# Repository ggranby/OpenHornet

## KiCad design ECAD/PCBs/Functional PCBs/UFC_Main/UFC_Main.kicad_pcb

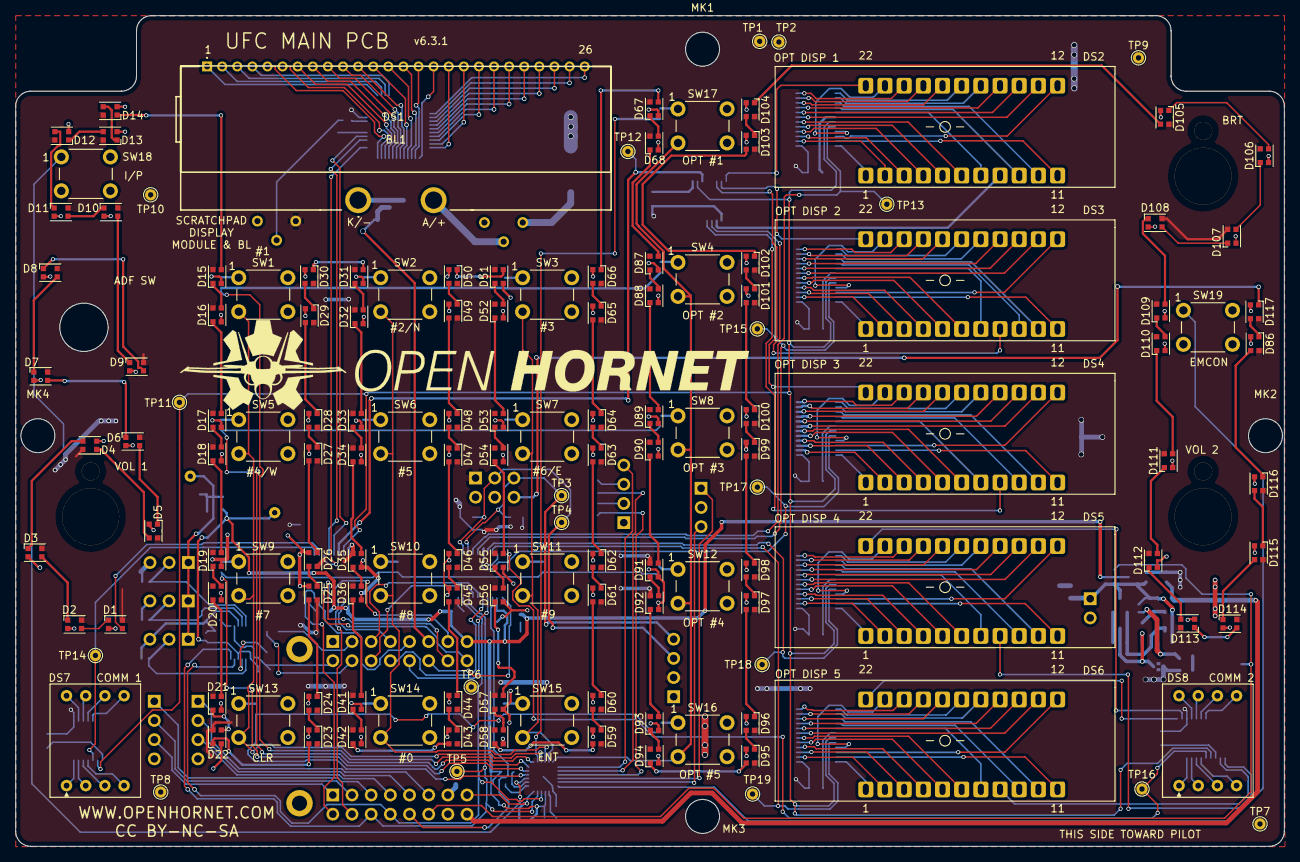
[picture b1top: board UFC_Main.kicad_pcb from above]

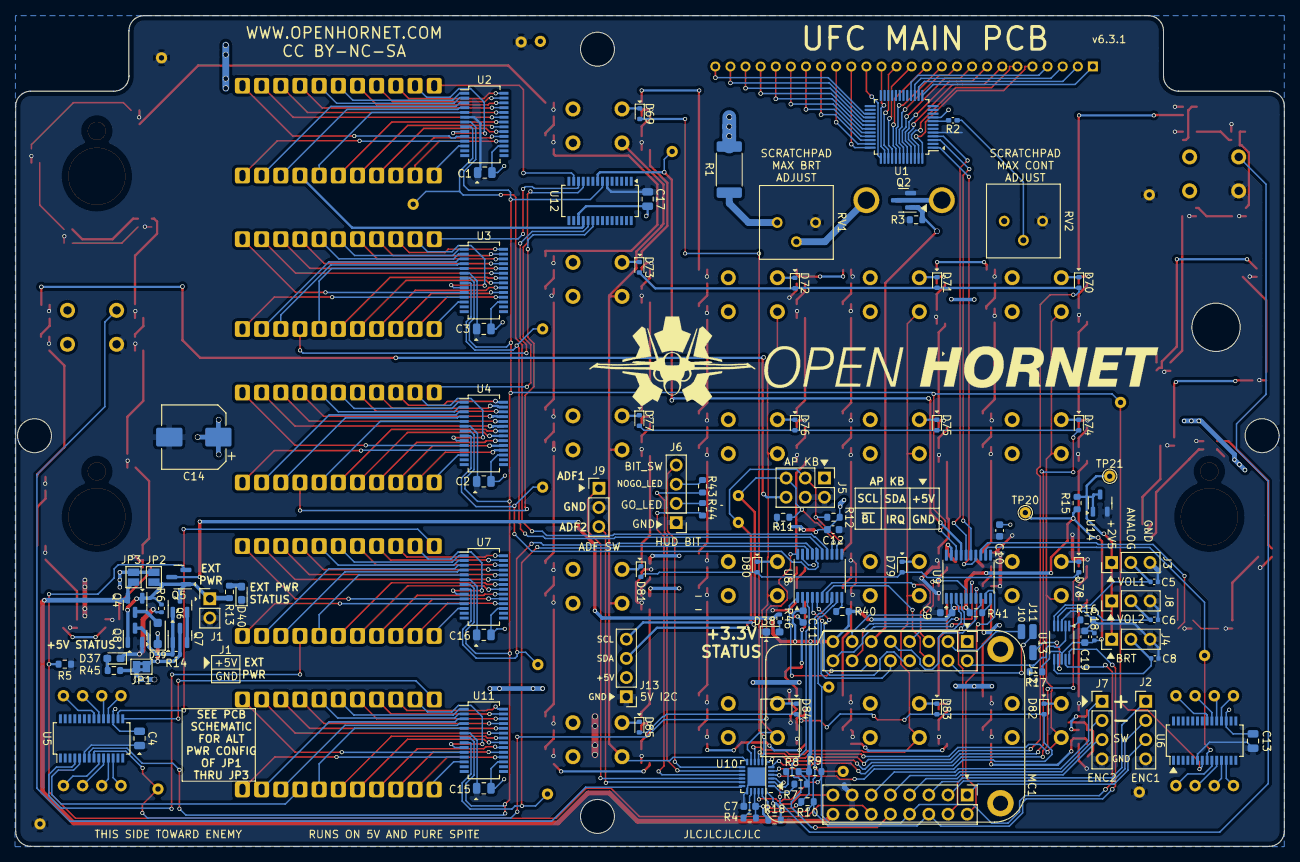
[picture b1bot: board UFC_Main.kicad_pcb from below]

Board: 2 copper layers, 168.0 x 110.0 mm, 257 parts (105 on the bottom side), 353 nets.

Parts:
BL1: SCR BL; SCRATCHPADBACKLIGHT
C1, C2, C3, C4, C13, C15, C16, C17: 10uF; C_0805_2012Metric
C5, C6, C8: 100nF; C_0402_1005Metric
C7, C9, C10, C11, C12, C19: .1uF; C_0603_1608Metric
C14: 1000uF; CP_Elec_8x10
C18: 10uF; C_0402_1005Metric
D1, D2, D3, D4, D5, D6, D7, D8, D9, D10, D11, D12, D13, D14, D15, D16, D17, D18, D19, D20, D21, D22, D23, D24, D25, D26, D27, D28, D29, D30, D31, D32, D33, D34, D35, D36, D41, D42, D43, D44, D45, D46, D47, D48, D49, D50, D51, D52, D53, D54, D55, D56, D57, D58, D59, D60, D61, D62, D63, D64, D65, D66, D67, D68, D86, D87, D88, D89, D90, D91, D92, D93, D94, D95, D96, D97, D98, D99, D100, D101, D102, D103, D104, D105, D106, D107, D108, D109, D110, D111, D112, D113, D114, D115, D116, D117: WS2812B-2020; LED_WS2812B-2020_PLCC4_2.0x2.0mm
D37: +5V_PWR; LED_0603_1608Metric_Pad1.05x0.95mm_HandSolder
D38: +3.3V_PWR; LED_0603_1608Metric_Pad1.05x0.95mm_HandSolder
D39: K24; D_SOD-123F
D40: EXT PWR; LED_0603_1608Metric_Pad1.05x0.95mm_HandSolder
D69, D70, D71, D72, D73, D74, D75, D76, D77, D78, D79, D80, D81, D82, D83, D84, D85: 1N4148WT; D_SOD-523
DS1: SCR DISP; SCRATCHPADLCD
DS2, DS3, DS4, DS5, DS6: UFCOptionDigit; UFCOptionDigitV3RectanglePads
DS7, DS8: UFCSingleDigit
J1: EXT_PWR; PinHeader_1x02_P2.54mm_Vertical
J2: ENC1; PinHeader_1x04_P2.54mm_Vertical
J3: VOL1; PinHeader_1x03_P2.54mm_Vertical
J4: BRT; PinHeader_1x03_P2.54mm_Vertical
J5: AP KB; PinHeader_2x03_P2.54mm_Vertical
J6: HUD BIT; PinHeader_1x04_P2.54mm_Vertical
J7: ENC2; PinHeader_1x04_P2.54mm_Vertical
J8: VOL2; PinHeader_1x03_P2.54mm_Vertical
J9: ADF SW; PinHeader_1x03_P2.54mm_Vertical
J10: GPIO3; SolderWirePad_1x01_SMD_1x2mm
J11: GPIO2; SolderWirePad_1x01_SMD_1x2mm
J12: AIN3; SolderWirePad_1x01_SMD_1x2mm
J13: 5V I2C; PinHeader_1x04_P2.54mm_Vertical
JP1: 5VP; SolderJumper-2_P1.3mm_Bridged2Bar_Pad1.0x1.5mm
JP2: VCC; SolderJumper-2_P1.3mm_Open_Pad1.0x1.5mm
JP3: VBUS; SolderJumper-2_P1.3mm_Open_Pad1.0x1.5mm
LOGO: LOGO; LOGO_OH_Text_Large
MC1: S2_MINI
MK1, MK2, MK3, MK4: MH; MountingHole_4.5mm
MK5: SW_ADF; MountingHole_6.4mm_M6
POT1: VOL1; BR10K_Pot_11mm_x_11mm
POT2: VOL2; BR10K_Pot_11mm_x_11mm
POT3: BRT; BR10K_Pot_11mm_x_11mm
Q2: 2N7002; SOT-23
Q4, Q6, Q7: SKML5203; SOT-23
Q5, Q8: SI2302; SOT-23
R1: 10; R_2512_6332Metric_Pad1.40x3.35mm_HandSolder
R2: 10; C_0402_1005Metric_Pad0.74x0.62mm_HandSolder
R3, R5, R7, R8: 10K; R_0603_1608Metric
R4, R9, R10, R11, R12, R18, R40, R41: 4.7k; R_0603_1608Metric
R6, R14: 100K; R_0402_1005Metric
R13, R15, R43, R44, R45: 120; R_0603_1608Metric
R16, R17: 4.7K; R_0603_1608Metric
R46: 33; R_0402_1005Metric
RV1: 1K; Potentiometer_Bourns_3386P_Vertical
RV2: 10K; Potentiometer_Bourns_3386P_Vertical
SW1, SW2, SW3, SW4, SW5, SW6, SW7, SW8, SW9, SW10, SW11, SW12, SW13, SW14, SW15, SW16, SW17, SW18, SW19: B3F-1026; Omron_B3F-1026
TP1: 5V; TestPoint_THTPad_D1.5mm_Drill0.7mm
TP2, TP7, TP8, TP9, TP10: GND; TestPoint_THTPad_D1.5mm_Drill0.7mm
TP3: SCL; TestPoint_THTPad_D1.5mm_Drill0.7mm
TP4: SDA; TestPoint_THTPad_D1.5mm_Drill0.7mm
TP5: SCL@3.3V; TestPoint_THTPad_D1.5mm_Drill0.7mm
TP6: SDA@3.3V; TestPoint_THTPad_D1.5mm_Drill0.7mm
TP11: DIO; TestPoint_THTPad_D1.5mm_Drill0.7mm
TP12: CUE_CLK; TestPoint_THTPad_D1.5mm_Drill0.7mm
TP13: OP1_CLK; TestPoint_THTPad_D1.5mm_Drill0.7mm
TP14: C1_CLK; TestPoint_THTPad_D1.5mm_Drill0.7mm
TP15: OP2_CLK; TestPoint_THTPad_D1.5mm_Drill0.7mm
TP16: C2_CLK; TestPoint_THTPad_D1.5mm_Drill0.7mm
TP17: OP3_CLK; TestPoint_THTPad_D1.5mm_Drill0.7mm
TP18: OP4_CLK; TestPoint_THTPad_D1.5mm_Drill0.7mm
TP19: OP5_CLK; TestPoint_THTPad_D1.5mm_Drill0.7mm
TP20: 3V3; TestPoint_THTPad_D1.5mm_Drill0.7mm
TP21: 2V5; TestPoint_THTPad_D1.5mm_Drill0.7mm
U1: HT1621B; LQFP-48_7x7mm_P0.5mm
U2, U3, U4, U5, U6, U7, U11, U12: GN1640T; SSOP-28_3.9x9.9mm_P0.635mm
U8, U9: TXS0108EPWR; TSSOP-20_4.4x6.5mm_P0.65mm
U10: TCA8418RTWR; WQFN-24-1EP_4x4mm_P0.5mm_EP2.45x2.45mm
U13: ADS1115IDGSR; VSSOP-10_3x3mm_P0.5mm
U14: ADR5040ARTZ; SOT-23-3

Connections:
+2V5: J3.1, J4.1, J8.1, R15.2, TP21.1 (1_1), U14.1 (V+), U14.3 (T)
+3V3: C7.2, C9.2, C11.2, C18.2, C19.2, MC1.8 (+3.3V), Q5.3 (D), R4.1, R7.2, R8.2, R9.1, R10.2, R15.1, R17.1, R18.1, R40.2, R41.2, R46.1, TP20.1 (1_1), U8.2 (VCCA), U9.2 (VCCA), U10.21 (VCC), U13.8 (VDD)
+5V: C1.2, C2.2, C3.2, C4.2, C10.2, C12.2, C13.2, C14.1, C15.2, C16.2, C17.2, D1.4 (VSS), D2.4 (VSS), D3.4 (VSS), D4.4 (VSS), D5.4 (VSS), D6.4 (VSS), D7.4 (VSS), D8.4 (VSS), D9.4 (VSS), D10.4 (VSS), D11.4 (VSS), D12.4 (VSS), D13.4 (VSS), D14.4 (VSS), D15.4 (VSS), D16.4 (VSS), D17.4 (VSS), D18.4 (VSS), D19.4 (VSS), D20.4 (VSS), D21.4 (VSS), D22.4 (VSS), D23.4 (VSS), D24.4 (VSS), D25.4 (VSS), D26.4 (VSS), D27.4 (VSS), D28.4 (VSS), D29.4 (VSS), D30.4 (VSS), D31.4 (VSS), D32.4 (VSS), D33.4 (VSS), D34.4 (VSS), D35.4 (VSS), D36.4 (VSS), D41.4 (VSS), D42.4 (VSS), D43.4 (VSS), D44.4 (VSS), D45.4 (VSS), D46.4 (VSS), D47.4 (VSS), D48.4 (VSS), D49.4 (VSS), D50.4 (VSS), D51.4 (VSS), D52.4 (VSS), D53.4 (VSS), D54.4 (VSS), D55.4 (VSS), D56.4 (VSS), D57.4 (VSS), D58.4 (VSS), D59.4 (VSS), D60.4 (VSS), D61.4 (VSS), D62.4 (VSS), D63.4 (VSS), D64.4 (VSS), D65.4 (VSS), D66.4 (VSS), D67.4 (VSS), D68.4 (VSS), D86.4 (VSS), D87.4 (VSS), D88.4 (VSS), D89.4 (VSS), D90.4 (VSS), D91.4 (VSS), D92.4 (VSS), D93.4 (VSS), D94.4 (VSS), D95.4 (VSS), D96.4 (VSS), D97.4 (VSS), D98.4 (VSS), D99.4 (VSS), D100.4 (VSS), D101.4 (VSS), D102.4 (VSS), D103.4 (VSS), D104.4 (VSS), D105.4 (VSS), D106.4 (VSS), D107.4 (VSS), D108.4 (VSS), D109.4 (VSS), D110.4 (VSS), D111.4 (VSS), D112.4 (VSS), D113.4 (VSS), D114.4 (VSS), D115.4 (VSS), D116.4 (VSS), D117.4 (VSS), J5.1, J13.2, JP1.2 (B), JP2.2 (B), JP3.2 (B), R1.2, R11.1, R12.2, R45.1, RV2.1, TP1.1 (1_1), U1.9 (VDD), U2.17 (VDD), U3.17 (VDD), U4.17 (VDD), U5.17 (VDD), U6.17 (VDD), U7.17 (VDD), U8.19 (VCCB), U9.19 (VCCB), U11.17 (VDD), U12.17 (VDD)
/1A: DS2.20 (A), U2.28 (GRID11)
/1B: DS2.19 (B), U2.27 (GRID10)
/1C: DS2.18 (C), U2.26 (GRID9)
/1D: DS2.2 (D), U2.18 (GRID1)
/1DP: DS2.8 (C5/D5), U12.18 (GRID1)
/1E: DS2.3 (E), U2.19 (GRID2)
/1F: DS2.4 (F), U2.20 (GRID3)
/1G: DS2.5 (G), U2.21 (GRID4)
/1H: DS2.6 (H), U2.22 (GRID5)
/1I: DS2.13 (I), U2.23 (GRID6)
/1J: DS2.14 (J), U2.24 (GRID7)
/1K: DS2.15 (K), U2.25 (GRID8)
/1L: DS2.16 (L), U2.2 (GRID13)
/1M: DS2.17 (M), U2.1 (GRID12)
/1N: DS2.9 (N), U2.4 (GRID15)
/1O: DS2.10 (O), U2.3 (GRID14)
/1P: DS2.7, U2.5 (GRID16)
/2A: DS3.20 (A), U3.28 (GRID11)
/2B: DS3.19 (B), U3.27 (GRID10)
/2C: DS3.18 (C), U3.26 (GRID9)
/2D: DS3.2 (D), U3.18 (GRID1)
/2DP: DS3.8 (C5/D5), U12.19 (GRID2)
/2E: DS3.3 (E), U3.19 (GRID2)
/2F: DS3.4 (F), U3.20 (GRID3)
/2G: DS3.5 (G), U3.21 (GRID4)
/2H: DS3.6 (H), U3.22 (GRID5)
/2I: DS3.13 (I), U3.23 (GRID6)
/2J: DS3.14 (J), U3.24 (GRID7)
/2K: DS3.15 (K), U3.25 (GRID8)
/2L: DS3.16 (L), U3.2 (GRID13)
/2M: DS3.17 (M), U3.1 (GRID12)
/2N: DS3.9 (N), U3.4 (GRID15)
/2O: DS3.10 (O), U3.3 (GRID14)
/2P: DS3.7, U3.5 (GRID16)
/3A: DS4.20 (A), U4.28 (GRID11)
/3B: DS4.19 (B), U4.27 (GRID10)
/3C: DS4.18 (C), U4.26 (GRID9)
/3D: DS4.2 (D), U4.18 (GRID1)
/3DP: DS4.8 (C5/D5), U12.20 (GRID3)
/3E: DS4.3 (E), U4.19 (GRID2)
/3F: DS4.4 (F), U4.20 (GRID3)
/3G: DS4.5 (G), U4.21 (GRID4)
/3H: DS4.6 (H), U4.22 (GRID5)
/3I: DS4.13 (I), U4.23 (GRID6)
/3J: DS4.14 (J), U4.24 (GRID7)
/3K: DS4.15 (K), U4.25 (GRID8)
/3L: DS4.16 (L), U4.2 (GRID13)
/3M: DS4.17 (M), U4.1 (GRID12)
/3N: DS4.9 (N), U4.4 (GRID15)
/3O: DS4.10 (O), U4.3 (GRID14)
/3P: DS4.7, U4.5 (GRID16)
/4A: DS5.20 (A), U7.28 (GRID11)
/4B: DS5.19 (B), U7.27 (GRID10)
/4C: DS5.18 (C), U7.26 (GRID9)
/4D: DS5.2 (D), U7.18 (GRID1)
/4DP: DS5.8 (C5/D5), U5.4 (GRID15)
/4E: DS5.3 (E), U7.19 (GRID2)
/4F: DS5.4 (F), U7.20 (GRID3)
/4G: DS5.5 (G), U7.21 (GRID4)
/4H: DS5.6 (H), U7.22 (GRID5)
/4I: DS5.13 (I), U7.23 (GRID6)
/4J: DS5.14 (J), U7.24 (GRID7)
/4K: DS5.15 (K), U7.25 (GRID8)
/4L: DS5.16 (L), U7.2 (GRID13)
/4M: DS5.17 (M), U7.1 (GRID12)
/4N: DS5.9 (N), U7.4 (GRID15)
/4O: DS5.10 (O), U7.3 (GRID14)
/4P: DS5.7, U7.5 (GRID16)
/5A: DS6.20 (A), U11.28 (GRID11)
/5B: DS6.19 (B), U11.27 (GRID10)
/5C: DS6.18 (C), U11.26 (GRID9)
/5D: DS6.2 (D), U11.18 (GRID1)
/5DP: DS6.8 (C5/D5), U5.5 (GRID16)
/5E: DS6.3 (E), U11.19 (GRID2)
/5F: DS6.4 (F), U11.20 (GRID3)
/5G: DS6.5 (G), U11.21 (GRID4)
/5H: DS6.6 (H), U11.22 (GRID5)
/5I: DS6.13 (I), U11.23 (GRID6)
/5J: DS6.14 (J), U11.24 (GRID7)
/5K: DS6.15 (K), U11.25 (GRID8)
/5L: DS6.16 (L), U11.2 (GRID13)
/5M: DS6.17 (M), U11.1 (GRID12)
/5N: DS6.9 (N), U11.4 (GRID15)
/5O: DS6.10 (O), U11.3 (GRID14)
/5P: DS6.7, U11.5 (GRID16)
/ADF1: J9.1, U10.16 (COL7)
/ADF2: J9.3, U10.17 (COL8)
/AIN0: C6.2, J8.2, U13.4 (AIN0)
/AIN1: C5.2, J3.2, U13.5 (AIN1)
/AIN2: C8.2, J4.2, U13.6 (AIN2)
/BIT_SW: J6.4, U10.13 (COL4)
/BL_DATA2: D8.1 (DOUT), D9.3 (DIN)
/BL_DATA3: D16.1 (DOUT), D17.3 (DIN)
/BL_DATA4: D24.1 (DOUT), D25.3 (DIN)
/BL_DATA5: D32.1 (DOUT), D33.3 (DIN)
/BL_DATA6: D44.1 (DOUT), D45.3 (DIN)
/BL_DATA7: D52.1 (DOUT), D53.3 (DIN)
/BL_DATA8: D60.1 (DOUT), D61.3 (DIN)
/BL_DATA9: D68.1 (DOUT), D87.3 (DIN)
/BL_DATA10: D93.1 (DOUT), D94.3 (DIN)
/BL_DATA11: D101.1 (DOUT), D102.3 (DIN)
/BL_DATA12: D109.1 (DOUT), D110.3 (DIN)
/C1_GRID1: DS7.8, U6.18 (GRID1)
/C1_GRID2: DS7.7, U6.19 (GRID2)
/C1_GRID3: DS7.6, U6.20 (GRID3)
/C1_GRID4: DS7.5, U6.21 (GRID4)
/C1_SEG1: DS7.4, U6.9 (SEG1)
/C1_SEG2: DS7.3, U6.10 (SEG2)
/C1_SEG3: DS7.2, U6.11 (SEG3)
/C1_SEG4: DS7.1, U6.12 (SEG4)
/COL0: SW1.3, SW5.3, SW9.3, SW13.3, U10.9 (COL0)
/COL1: SW2.3, SW6.3, SW10.3, SW14.3, U10.10 (COL1)
/COL2: SW3.3, SW7.3, SW11.3, SW15.3, U10.11 (COL2)
/COL3: SW4.3, SW8.3, SW12.3, SW16.3, SW17.3, U10.12 (COL3)
/COM0: DS1.1 (COM1), U1.13 (COM0)
/COM1: DS1.2 (COM2), U1.14 (COM1)
/COM2: DS1.3 (COM3), U1.15 (COM2)
/COM3: DS1.4 (COM4), U1.16 (COM3)
/C_GRID1: DS8.8, U5.18 (GRID1)
/C_GRID2: DS8.7, U5.19 (GRID2)
/C_GRID3: DS8.6, U5.20 (GRID3)
/C_GRID4: DS8.5, U5.21 (GRID4)
/C_SEG1: DS8.4, U5.9 (SEG1)
/C_SEG2: DS8.3, U5.10 (SEG2)
/C_SEG3: DS8.2, U5.11 (SEG3)
/C_SEG4: DS8.1, U5.12 (SEG4)
/GO_LED: J6.2, R44.2
/NOGO_LED: J6.3, R43.2
/OP1D1: DS2.1 (DIG1), U2.12 (SEG4)
/OP1D2: DS2.21 (DIG2), U2.9 (SEG1)
/OP1D3: DS2.12 (DIG3), U2.10 (SEG2)
/OP1D4: DS2.11 (DIG4), U2.11 (SEG3)
/OP1D5: DS2.22 (DIG5), U12.13 (SEG5)
/OP2D1: DS3.1 (DIG1), U3.12 (SEG4)
/OP2D2: DS3.21 (DIG2), U3.9 (SEG1)
/OP2D3: DS3.12 (DIG3), U3.10 (SEG2)
/OP2D4: DS3.11 (DIG4), U3.11 (SEG3)
/OP2D5: DS3.22 (DIG5), U12.12 (SEG4)
/OP3D1: DS4.1 (DIG1), U4.12 (SEG4)
/OP3D2: DS4.21 (DIG2), U4.9 (SEG1)
/OP3D3: DS4.12 (DIG3), U4.10 (SEG2)
/OP3D4: DS4.11 (DIG4), U4.11 (SEG3)
/OP3D5: DS4.22 (DIG5), U12.11 (SEG3)
/OP4D1: DS5.1 (DIG1), U7.12 (SEG4)
/OP4D2: DS5.21 (DIG2), U7.9 (SEG1)
/OP4D3: DS5.12 (DIG3), U7.10 (SEG2)
/OP4D4: DS5.11 (DIG4), U7.11 (SEG3)
/OP4D5: DS5.22 (DIG5), U5.16 (SEG8)
/OP5D1: DS6.1 (DIG1), U11.12 (SEG4)
/OP5D2: DS6.21 (DIG2), U11.9 (SEG1)
/OP5D3: DS6.12 (DIG3), U11.10 (SEG2)
/OP5D4: DS6.11 (DIG4), U11.11 (SEG3)
/OP5D5: DS6.22 (DIG5), U5.15 (SEG7)
/ROW0: D69.2 (A), U10.8 (ROW0)
/ROW1: D70.2 (A), D71.2 (A), D72.2 (A), D73.2 (A), U10.7 (ROW1)
/ROW2: D74.2 (A), D75.2 (A), D76.2 (A), D77.2 (A), U10.6 (ROW2)
/ROW3: D78.2 (A), D79.2 (A), D80.2 (A), D81.2 (A), U10.5 (ROW3)
/ROW4: D82.2 (A), D83.2 (A), D84.2 (A), D85.2 (A), U10.4 (ROW4)
/SEG0: DS1.5 (9D1/9E/9F/9A1), U1.48 (SEG0)
/SEG1: DS1.6 (9K/9G1/9H/9I), U1.47 (SEG1)
/SEG2: DS1.7 (9L/9M/9G2/9J), U1.46 (SEG2)
/SEG3: DS1.8 (9D2/9C/9B/9A2), U1.45 (SEG3)
/SEG4: DS1.9 (8D1/8E/8F/8A1), U1.44 (SEG4)
/SEG5: DS1.10 (8K/8G1/8H/8I), U1.43 (SEG5)
/SEG6: DS1.11 (8L/8M/8G2/8J), U1.42 (SEG6)
/SEG7: DS1.12 (8D2/8C/8B/8A2), U1.41 (SEG7)
/SEG8: DS1.13 (7E/7F/7A), U1.40 (SEG8)
/SEG9: DS1.14 (7D/7C/7G/7B), U1.39 (SEG9)
/SEG10: DS1.15 (6E/6F/6A), U1.38 (SEG10)
/SEG11: DS1.16 (6D/6C/6G/6B), U1.37 (SEG11)
/SEG12: DS1.17 (5E/5F/5A), U1.36 (SEG12)
/SEG13: DS1.18 (5D/5C/5G/5B), U1.35 (SEG13)
/SEG14: DS1.19 (4E/4F/4A), U1.34 (SEG14)
/SEG15: DS1.20 (4D/4C/4G/4B), U1.33 (SEG15)
/SEG16: DS1.21 (3E/3F/3A), U1.32 (SEG16)
/SEG17: DS1.22 (3D/3C/3G/3B), U1.31 (SEG17)
/SEG18: DS1.23 (2E/2F/2A), U1.30 (SEG18)
/SEG19: DS1.24 (2D/2C/2G/2B), U1.29 (SEG19)
/SEG20: DS1.25 (1E/1F/1A), U1.28 (SEG20)
/SEG21: DS1.26 (1D/1C/1G/1B), U1.27 (SEG21)
/SW13: SW18.1, U10.3 (ROW5)
/SW19: SW19.1, U10.18 (COL9)
ADC_RDY@3.3V: MC1.9 (IO1), R17.2, U13.2 (ALERT/RDY)
COM1_CLK: TP14.1 (1_1), U6.8 (SCLK), U9.12 (B8)
COM1_CLK@3.3V: MC1.25 (IO39), U9.9 (A8)
COM2_CLK: TP16.1 (1_1), U5.8 (SCLK), U8.20 (B1)
COM2_CLK@3.3V: MC1.14 (IO10), U8.1 (A1)
CUE_CLK: TP12.1 (1_1), U9.17 (B3), U12.8 (SCLK)
CUE_CLK@3.3V: MC1.26 (IO37), U9.4 (A3)
DIO: TP11.1 (1_1), U2.7 (DATA), U3.7 (DATA), U4.7 (DATA), U5.7 (DATA), U6.7 (DATA), U7.7 (DATA), U9.18 (B2), U11.7 (DATA), U12.7 (DATA)
DIO@3.3V: MC1.4 (IO7/SCK), U9.3 (A2)
ENC1+: J2.1, MC1.19 (IO36)
ENC1-: J2.2, MC1.18 (IO38)
ENC1PB: J2.3, MC1.17 (IO40)
ENC2+: J7.1, MC1.22 (IO17/DAC1)
ENC2-: J7.2, MC1.21 (IO21)
ENC2PB: J7.3, MC1.20 (IO34)
GND: C1.1, C2.1, C3.1, C4.1, C5.1, C6.1, C7.1, C8.1, C9.1, C10.1, C11.1, C12.1, C13.1, C14.2, C15.1, C16.1, C17.1, C18.1, C19.1, D1.2 (GND), D2.2 (GND), D3.2 (GND), D4.2 (GND), D5.2 (GND), D6.2 (GND), D7.2 (GND), D8.2 (GND), D9.2 (GND), D10.2 (GND), D11.2 (GND), D12.2 (GND), D13.2 (GND), D14.2 (GND), D15.2 (GND), D16.2 (GND), D17.2 (GND), D18.2 (GND), D19.2 (GND), D20.2 (GND), D21.2 (GND), D22.2 (GND), D23.2 (GND), D24.2 (GND), D25.2 (GND), D26.2 (GND), D27.2 (GND), D28.2 (GND), D29.2 (GND), D30.2 (GND), D31.2 (GND), D32.2 (GND), D33.2 (GND), D34.2 (GND), D35.2 (GND), D36.2 (GND), D37.1 (K), D38.1 (K), D40.1 (K), D41.2 (GND), D42.2 (GND), D43.2 (GND), D44.2 (GND), D45.2 (GND), D46.2 (GND), D47.2 (GND), D48.2 (GND), D49.2 (GND), D50.2 (GND), D51.2 (GND), D52.2 (GND), D53.2 (GND), D54.2 (GND), D55.2 (GND), D56.2 (GND), D57.2 (GND), D58.2 (GND), D59.2 (GND), D60.2 (GND), D61.2 (GND), D62.2 (GND), D63.2 (GND), D64.2 (GND), D65.2 (GND), D66.2 (GND), D67.2 (GND), D68.2 (GND), D86.2 (GND), D87.2 (GND), D88.2 (GND), D89.2 (GND), D90.2 (GND), D91.2 (GND), D92.2 (GND), D93.2 (GND), D94.2 (GND), D95.2 (GND), D96.2 (GND), D97.2 (GND), D98.2 (GND), D99.2 (GND), D100.2 (GND), D101.2 (GND), D102.2 (GND), D103.2 (GND), D104.2 (GND), D105.2 (GND), D106.2 (GND), D107.2 (GND), D108.2 (GND), D109.2 (GND), D110.2 (GND), D111.2 (GND), D112.2 (GND), D113.2 (GND), D114.2 (GND), D115.2 (GND), D116.2 (GND), D117.2 (GND), J1.2, J2.4, J3.3, J4.3, J5.2, J5.4, J6.1, J7.4, J8.3, J9.2, J13.1, MC1.23 (GND1), MC1.31 (GND2), Q2.2 (S), Q8.2 (S), R3.1, R5.2, R6.2, R16.2, RV1.3, RV2.3, SW18.3, SW19.3, TP2.1 (1_1), TP7.1 (1_1), TP8.1 (1_1), TP9.1 (1_1), TP10.1 (1_1), U1.5 (VSS), U2.6 (GND), U3.6 (GND), U4.6 (GND), U5.6 (GND), U6.6 (GND), U7.6 (GND), U8.11 (GND), U9.11 (GND), U10.19 (GND), U10.25 (GND_PAD), U11.6 (GND), U12.6 (GND), U13.3 (GND), U14.2 (V-)
IO_INT: MC1.24 (IO15), R18.2, U10.24 (INT)
KB_BL: D117.1 (DOUT), J5.6
unnamed: BL1.2 (A), RV1.2
unnamed: BL1.1 (K), Q2.3 (D)
unnamed: D1.1 (DOUT), D2.3 (DIN)
unnamed: D2.1 (DOUT), D3.3 (DIN)
unnamed: D3.1 (DOUT), D4.3 (DIN)
unnamed: D4.1 (DOUT), D5.3 (DIN)
unnamed: D5.1 (DOUT), D6.3 (DIN)
unnamed: D6.1 (DOUT), D7.3 (DIN)
unnamed: D7.1 (DOUT), D8.3 (DIN)
unnamed: D9.1 (DOUT), D10.3 (DIN)
unnamed: D10.1 (DOUT), D11.3 (DIN)
unnamed: D11.1 (DOUT), D12.3 (DIN)
unnamed: D12.1 (DOUT), D13.3 (DIN)
unnamed: D13.1 (DOUT), D14.3 (DIN)
unnamed: D14.1 (DOUT), D15.3 (DIN)
unnamed: D15.1 (DOUT), D16.3 (DIN)
unnamed: D17.1 (DOUT), D18.3 (DIN)
unnamed: D18.1 (DOUT), D19.3 (DIN)
unnamed: D19.1 (DOUT), D20.3 (DIN)
unnamed: D20.1 (DOUT), D21.3 (DIN)
unnamed: D21.1 (DOUT), D22.3 (DIN)
unnamed: D22.1 (DOUT), D23.3 (DIN)
unnamed: D23.1 (DOUT), D24.3 (DIN)
unnamed: D25.1 (DOUT), D26.3 (DIN)
unnamed: D26.1 (DOUT), D27.3 (DIN)
unnamed: D27.1 (DOUT), D28.3 (DIN)
unnamed: D28.1 (DOUT), D29.3 (DIN)
unnamed: D29.1 (DOUT), D30.3 (DIN)
unnamed: D30.1 (DOUT), D31.3 (DIN)
unnamed: D31.1 (DOUT), D32.3 (DIN)
unnamed: D33.1 (DOUT), D34.3 (DIN)
unnamed: D34.1 (DOUT), D35.3 (DIN)
unnamed: D35.1 (DOUT), D36.3 (DIN)
unnamed: D36.1 (DOUT), D41.3 (DIN)
unnamed: D37.2 (A), R45.2
unnamed: D38.2 (A), R46.2
unnamed: D39.2 (A), Q4.3 (D)
unnamed: D39.1 (K), JP1.1 (A), Q7.3 (D), R14.1
unnamed: D40.2 (A), R13.2
unnamed: D41.1 (DOUT), D42.3 (DIN)
unnamed: D42.1 (DOUT), D43.3 (DIN)
unnamed: D43.1 (DOUT), D44.3 (DIN)
unnamed: D45.1 (DOUT), D46.3 (DIN)
unnamed: D46.1 (DOUT), D47.3 (DIN)
unnamed: D47.1 (DOUT), D48.3 (DIN)
unnamed: D48.1 (DOUT), D49.3 (DIN)
unnamed: D49.1 (DOUT), D50.3 (DIN)
unnamed: D50.1 (DOUT), D51.3 (DIN)
unnamed: D51.1 (DOUT), D52.3 (DIN)
unnamed: D53.1 (DOUT), D54.3 (DIN)
unnamed: D54.1 (DOUT), D55.3 (DIN)
unnamed: D55.1 (DOUT), D56.3 (DIN)
unnamed: D56.1 (DOUT), D57.3 (DIN)
unnamed: D57.1 (DOUT), D58.3 (DIN)
unnamed: D58.1 (DOUT), D59.3 (DIN)
unnamed: D59.1 (DOUT), D60.3 (DIN)
unnamed: D61.1 (DOUT), D62.3 (DIN)
unnamed: D62.1 (DOUT), D63.3 (DIN)
unnamed: D63.1 (DOUT), D64.3 (DIN)
unnamed: D64.1 (DOUT), D65.3 (DIN)
unnamed: D65.1 (DOUT), D66.3 (DIN)
unnamed: D66.1 (DOUT), D67.3 (DIN)
unnamed: D67.1 (DOUT), D68.3 (DIN)
unnamed: D69.1 (K), SW17.1
unnamed: D70.1 (K), SW1.1
unnamed: D71.1 (K), SW2.1
unnamed: D72.1 (K), SW3.1
unnamed: D73.1 (K), SW4.1
unnamed: D74.1 (K), SW5.1
unnamed: D75.1 (K), SW6.1
unnamed: D76.1 (K), SW7.1
unnamed: D77.1 (K), SW8.1
unnamed: D78.1 (K), SW9.1
unnamed: D79.1 (K), SW10.1
unnamed: D80.1 (K), SW11.1
unnamed: D81.1 (K), SW12.1
unnamed: D82.1 (K), SW13.1
unnamed: D83.1 (K), SW14.1
unnamed: D84.1 (K), SW15.1
unnamed: D85.1 (K), SW16.1
unnamed: D87.1 (DOUT), D88.3 (DIN)
unnamed: D88.1 (DOUT), D89.3 (DIN)
unnamed: D89.1 (DOUT), D90.3 (DIN)
unnamed: D90.1 (DOUT), D91.3 (DIN)
unnamed: D91.1 (DOUT), D92.3 (DIN)
unnamed: D92.1 (DOUT), D93.3 (DIN)
unnamed: D94.1 (DOUT), D95.3 (DIN)
unnamed: D95.1 (DOUT), D96.3 (DIN)
unnamed: D96.1 (DOUT), D97.3 (DIN)
unnamed: D97.1 (DOUT), D98.3 (DIN)
unnamed: D98.1 (DOUT), D99.3 (DIN)
unnamed: D99.1 (DOUT), D100.3 (DIN)
unnamed: D100.1 (DOUT), D101.3 (DIN)
unnamed: D102.1 (DOUT), D103.3 (DIN)
unnamed: D103.1 (DOUT), D104.3 (DIN)
unnamed: D104.1 (DOUT), D105.3 (DIN)
unnamed: D105.1 (DOUT), D106.3 (DIN)
unnamed: D106.1 (DOUT), D107.3 (DIN)
unnamed: D107.1 (DOUT), D108.3 (DIN)
unnamed: D108.1 (DOUT), D109.3 (DIN)
unnamed: D110.1 (DOUT), D111.3 (DIN)
unnamed: D111.1 (DOUT), D112.3 (DIN)
unnamed: D112.1 (DOUT), D113.3 (DIN)
unnamed: D113.1 (DOUT), D114.3 (DIN)
unnamed: D114.1 (DOUT), D115.3 (DIN)
unnamed: D115.1 (DOUT), D116.3 (DIN)
unnamed: D86.3 (DIN), D116.1 (DOUT)
unnamed: D86.1 (DOUT), D117.3 (DIN)
unnamed: J10.1 (Pin_1_1), MC1.2 (IO3)
unnamed: J11.1 (Pin_1_1), MC1.10 (IO2)
unnamed: J12.1 (Pin_1_1), U13.7 (AIN3)
unnamed: Q6.1 (G), Q7.1 (G), Q8.3 (D), R14.2
unnamed: Q6.2 (S), Q7.2 (S)
unnamed: R1.1, RV1.1
unnamed: R2.1, RV2.2
unnamed: R2.2, U1.8 (VLCD)
unnamed: R40.1, U8.10 (OE)
unnamed: R41.1, U9.10 (OE)
unnamed: R43.1, U10.14 (COL5)
unnamed: R44.1, U10.15 (COL6)
unnamed: R4.2, U10.20 (RESET)
unnamed: R8.1, U10.2 (ROW6)
unnamed: R7.1, U10.1 (ROW7)
unnamed: R16.1, U13.1 (ADDR)
OP1_CLK: TP13.1 (1_1), U2.8 (SCLK), U8.14 (B6)
OP1_CLK@3.3V: MC1.11 (IO4), U8.7 (A6)
OP2_CLK: TP15.1 (1_1), U3.8 (SCLK), U8.15 (B5)
OP2_CLK@3.3V: MC1.3 (IO5), U8.6 (A5)
OP3_CLK: TP17.1 (1_1), U4.8 (SCLK), U8.16 (B4)
OP3_CLK@3.3V: MC1.12 (IO6), U8.5 (A4)
OP4_CLK: TP18.1 (1_1), U7.8 (SCLK), U8.17 (B3)
OP4_CLK@3.3V: MC1.13 (IO8), U8.4 (A3)
OP5_CLK: TP19.1 (1_1), U8.18 (B2), U11.8 (SCLK)
OP5_CLK@3.3V: MC1.29 (IO18/DAC2), U8.3 (A2)
PNL_BL: D1.3 (DIN), U9.13 (B7)
PNL_BL@3.3V: MC1.5 (IO9/MISO), U9.8 (A7)
SCL: J5.5, J13.4, R11.2, TP3.1 (1_1), U8.13 (B7)
SCL@3.3V: MC1.27 (IO35/SCL), R10.1, TP5.1 (1_1), U8.8 (A7), U10.23 (SCL), U13.10 (SCL)
SCRCS: U1.1 (~CS), U9.14 (B6)
SCRCS@3.3V: MC1.16 (IO14), U9.7 (A6)
SCRDATA: U1.4 (DATA), U9.16 (B4)
SCRDATA@3.3V: MC1.7 (IO12), U9.5 (A4)
SCRWR: U1.3 (~WR), U9.15 (B5)
SCRWR@3.3V: MC1.15 (IO13), U9.6 (A5)
SCR_BL@3.3V: MC1.6 (IO11/MOSI), Q2.1 (G), R3.2
SDA: J5.3, J13.3, R12.1, TP4.1 (1_1), U8.12 (B8)
SDA@3.3V: MC1.28 (IO33/SDA), R9.2, TP6.1 (1_1), U8.9 (A8), U10.22 (SDA), U13.9 (SDA)
VBUS: JP3.1 (A), MC1.32 (VBUS/+5V), Q4.2 (S)
VCC: J1.1, JP2.1 (A), Q4.1 (G), Q5.1 (G), Q6.3 (D), Q8.1 (G), R6.1, R13.1
VCC_SNS@3.3V: MC1.30 (IO16), Q5.2 (S), R5.1

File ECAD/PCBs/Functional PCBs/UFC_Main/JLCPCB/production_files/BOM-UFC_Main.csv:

Comment,Designator,Footprint,LCSC,Quantity
+3.3V_PWR,D38,LED_0603_1608Metric_Pad1.05x0.95mm_HandSolder,C72043,1
+5V_PWR,D37,LED_0603_1608Metric_Pad1.05x0.95mm_HandSolder,C72043,1
.1uF,"C10,C11,C12,C19,C7,C9",C_0603_1608Metric,C14663,6
10,R2,C_0402_1005Metric_Pad0.74x0.62mm_HandSolder,C25077,1
1000uF,C14,CP_Elec_8x10,C445083,1
100K,"R14,R6",R_0402_1005Metric,C25741,2
100nF,"C5,C6,C8",C_0402_1005Metric,C1525,3
10K,"R3,R5,R7,R8",R_0603_1608Metric,C25804,4
10uF,C18,C_0402_1005Metric,C15525,1
10uF,"C1,C13,C15,C16,C17,C2,C3,C4",C_0805_2012Metric,C15850,8
120,"R13,R15,R43,R44,R45",R_0603_1608Metric,C22787,5
1N4148WT,"D69,D70,D71,D72,D73,D74,D75,D76,D77,D78,D79,D80,D81,D82,D83,D84,D85",D_SOD-523,C727112,17
2N7002,Q2,SOT-23,C8545,1
33,R46,R_0402_1005Metric,C25105,1
4.7K,"R16,R17",R_0603_1608Metric,C23162,2
4.7k,"R10,R11,R12,R18,R4,R40,R41,R9",R_0603_1608Metric,C23162,8
ADR5040ARTZ,U14,SOT-23-3,C144273,1
ADS1115IDGSR,U13,VSSOP-10_3x3mm_P0.5mm,C37593,1
EXT PWR,D40,LED_0603_1608Metric_Pad1.05x0.95mm_HandSolder,C72043,1
GN1640T,"U11,U12,U2,U3,U4,U5,U6,U7",SSOP-28_3.9x9.9mm_P0.635mm,C2758330,8
HT1621B,U1,LQFP-48_7x7mm_P0.5mm,C7532,1
K24,D39,D_SOD-123F,C908664,1
SI2302,Q8,SOT-23,C2891732,1
SKML5203,"Q4,Q6,Q7",SOT-23,C475707,3
TCA8418RTWR,U10,WQFN-24-1EP_4x4mm_P0.5mm_EP2.45x2.45mm,C138713,1
TXS0108EPWR,"U8,U9",TSSOP-20_4.4x6.5mm_P0.65mm,C17206,2
WS2812B-2020,"D1,D10,D100,D101,D102,D103,D104,D105,D106,D107,D108,D109,D11,D110,D111,D112,D113,D114,D115,D116,D117,D12,D13,D14,D15,D16,D17,D18,D19,D2,D20,D21,D22,D23,D24,D25,D26,D27,D28,D29,D3,D30,D31,D32,D33,D34,D35,D36,D4,D41,D42,D43,D44,D45,D46,D47,D48,D49,D5,D50,D51,D52,D53,D54,D55,D56,D57,D58,D59,D6,D60,D61,D62,D63,D64,D65,D66,D67,D68,D7,D8,D86,D87,D88,D89,D9,D90,D91,D92,D93,D94,D95,D96,D97,D98,D99",LED_WS2812B-2020_PLCC4_2.0x2.0mm,C965555,96
S2_MINI,MC1,S2_MINI,,1
10,R1,R_2512_6332Metric_Pad1.40x3.35mm_HandSolder,,1
ADF SW,J9,PinHeader_1x03_P2.54mm_Vertical,,1
VOL2,J8,PinHeader_1x03_P2.54mm_Vertical,,1
ENC2,J7,PinHeader_1x04_P2.54mm_Vertical,,1
HUD BIT,J6,PinHeader_1x04_P2.54mm_Vertical,,1
AP KB,J5,PinHeader_2x03_P2.54mm_Vertical,,1
BRT,J4,PinHeader_1x03_P2.54mm_Vertical,,1
VOL1,J3,PinHeader_1x03_P2.54mm_Vertical,,1
ENC1,J2,PinHeader_1x04_P2.54mm_Vertical,,1
EXT_PWR,J1,PinHeader_1x02_P2.54mm_Vertical,,1
SCR DISP,DS1,SCRATCHPADLCD,,1
SCR BL,BL1,SCRATCHPADBACKLIGHT,,1
UFCOptionDigit,DS6,UFCOptionDigitV3RectanglePads,,1
UFCOptionDigit,DS5,UFCOptionDigitV3RectanglePads,,1
UFCOptionDigit,DS4,UFCOptionDigitV3RectanglePads,,1
UFCOptionDigit,DS3,UFCOptionDigitV3RectanglePads,,1
UFCOptionDigit,DS2,UFCOptionDigitV3RectanglePads,,1
UFCSingleDigit,DS8,UFCSingleDigit,,1
UFCSingleDigit,DS7,UFCSingleDigit,,1
VOL2,POT2,BR10K_Pot_11mm_x_11mm,,1
BRT,POT3,BR10K_Pot_11mm_x_11mm,,1
VOL1,POT1,BR10K_Pot_11mm_x_11mm,,1
SW_ADF,MK5,MountingHole_6.4mm_M6,,1
MH,MK1,MountingHole_4.5mm,,1
MH,MK2,MountingHole_4.5mm,,1
MH,MK3,MountingHole_4.5mm,,1
MH,MK4,MountingHole_4.5mm,,1
B3F-1026,SW1,Omron_B3F-1026,,1
B3F-1026,SW2,Omron_B3F-1026,,1
B3F-1026,SW3,Omron_B3F-1026,,1
B3F-1026,SW4,Omron_B3F-1026,,1
B3F-1026,SW5,Omron_B3F-1026,,1
B3F-1026,SW6,Omron_B3F-1026,,1
B3F-1026,SW7,Omron_B3F-1026,,1
B3F-1026,SW8,Omron_B3F-1026,,1
B3F-1026,SW9,Omron_B3F-1026,,1
B3F-1026,SW10,Omron_B3F-1026,,1
B3F-1026,SW11,Omron_B3F-1026,,1
B3F-1026,SW12,Omron_B3F-1026,,1
B3F-1026,SW13,Omron_B3F-1026,,1
B3F-1026,SW14,Omron_B3F-1026,,1
B3F-1026,SW15,Omron_B3F-1026,,1
B3F-1026,SW16,Omron_B3F-1026,,1
B3F-1026,SW17,Omron_B3F-1026,,1
B3F-1026,SW18,Omron_B3F-1026,,1
B3F-1026,SW19,Omron_B3F-1026,,1
SI2302,Q5,SOT-23,,1
1K,RV1,Potentiometer_Bourns_3386P_Vertical,,1
10K,RV2,Potentiometer_Bourns_3386P_Vertical,,1
AIN3,J12,SolderWirePad_1x01_SMD_1x2mm,,1
GPIO2,J11,SolderWirePad_1x01_SMD_1x2mm,,1
GPIO3,J10,SolderWirePad_1x01_SMD_1x2mm,,1

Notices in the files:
ECAD/PCBs/Functional PCBs/UFC_Main/UFC_Main.kicad_pcb:
CC BY-NC-SA
